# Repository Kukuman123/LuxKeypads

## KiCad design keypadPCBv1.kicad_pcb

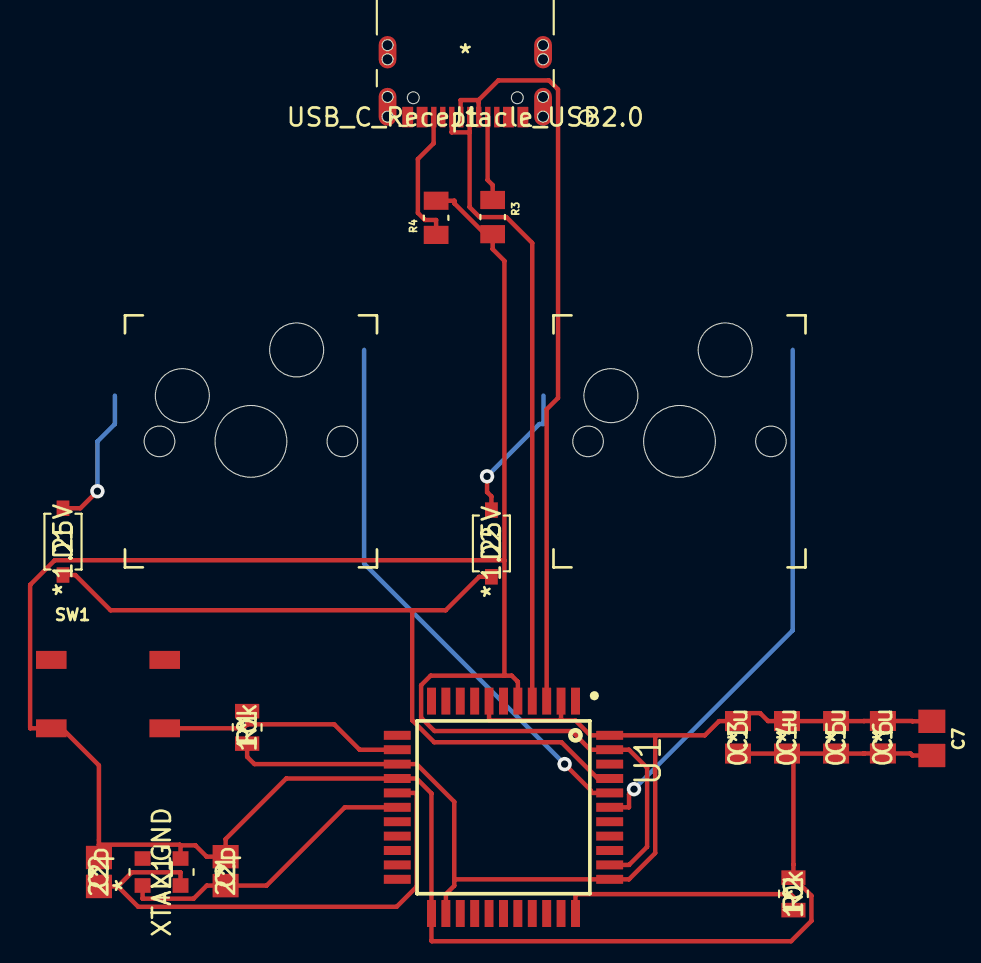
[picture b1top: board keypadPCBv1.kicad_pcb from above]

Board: 2 copper layers, 19 parts (0 on the bottom side), 15 nets.

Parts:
C1, C2: 22p; C0805C220J5GAC7800
C3, C4, C5, C6: 0.1u; CC0805ZRY5V9BB104
C7: 4.7u; CAPC2012X135
D1, D2: 1.25V; 1N4148W-TP
J1: USB_C_Receptacle_USB2.0; USB4105-GF-A
K1, K2: KEYSW; Kailh_socket_MX
R1, R2: 10k; RMCF0805JT10K0
R3, R4: 5.1k; RESC2012X65N
SW1: SW_PUSH; SW_TL3342F160QG_TR
U1: ATMEGA32U4-AU; QFP80P1200X1200X120-44N
X1: XTAL_GND; FA-238 16.0000MB-C3

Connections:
+5V: C1.2, C2.2, C3.2, C4.2, C5.2, C6.2, C7.2, R2.2, R3.2, R4.2, SW1.1, U1.5 (UGnd), U1.15 (GND), U1.23 (GND), U1.35 (GND), U1.43 (GND), X1.3
unnamed: C1.1, U1.17 (XTAL1), X1.1
unnamed: C2.1, U1.16 (XTAL2), X1.2
unnamed: D1.2 (A), K1.2
unnamed: D2.2 (A), K2.2
unnamed: J1.A5 (CC1), R3.1
unnamed: J1.A6 (D+), J1.B6 (D+), U1.4 (D+)
unnamed: J1.A7 (D-), J1.B7 (D-), U1.3 (D-)
unnamed: J1.B5 (CC2), R4.1
unnamed: R1.2, SW1.2, U1.13 (RESET*)
unnamed: R2.1, U1.33 (PE2_HWB*)
VCC: C3.1, C4.1, C5.1, C6.1, C7.1, R1.1, U1.2 (UVcc), U1.7 (VBus), U1.14 (VCC), U1.24 (AVCC), U1.34 (VCC), U1.44 (AVCC)
col0: K1.1, U1.40 (PF1_ADC1)
col1: K2.1, U1.39 (PF4_ADC4/TCK)
row0: D1.1 (K), D2.1 (K), U1.41 (PF0_ADC0)

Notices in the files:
parts and their libraries:
Copyright 2021 Accelerated Designs. All rights reserved.
